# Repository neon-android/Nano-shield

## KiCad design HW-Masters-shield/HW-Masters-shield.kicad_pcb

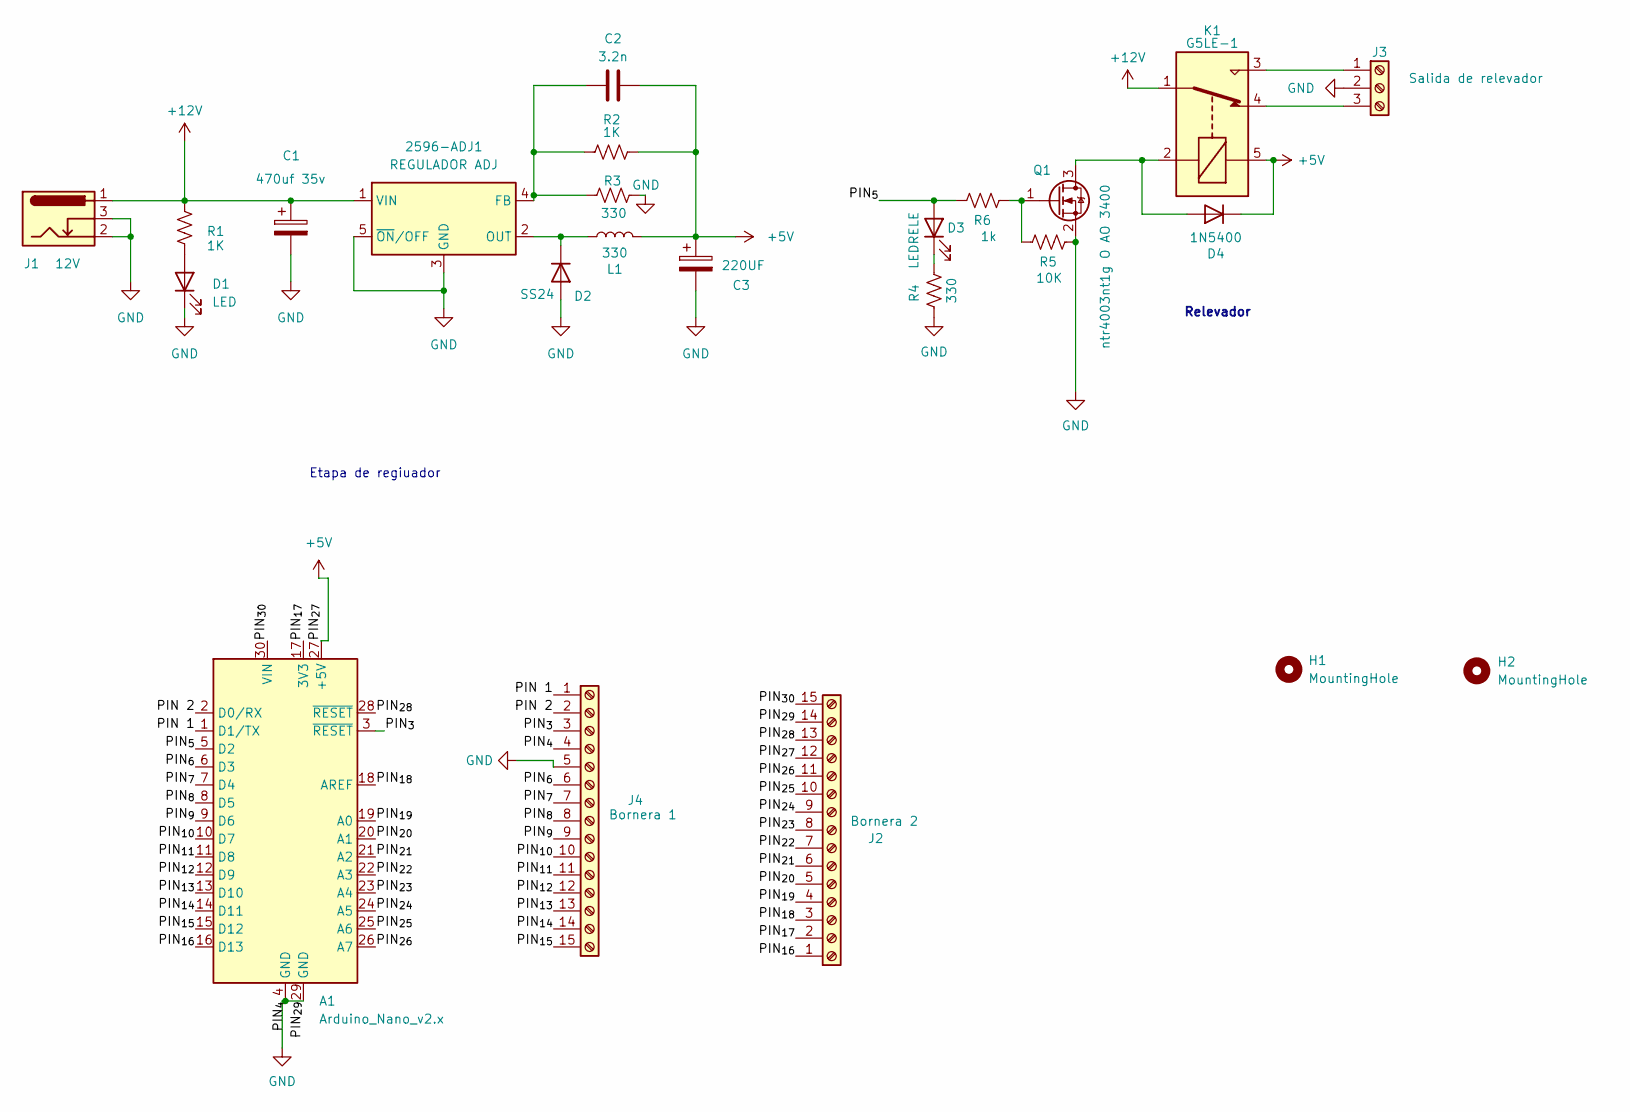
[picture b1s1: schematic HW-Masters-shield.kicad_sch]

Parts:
2596-ADJ1: REGULADOR ADJ; TO-263-5_TabPin3
A1: Arduino_Nano_v2.x; Arduino_Nano
C1: 470uf 35v; CP_Radial_D6.3mm_P2.50mm
C2: 3.2n; C_0805_2012Metric
C3: 220UF; CP_Radial_D6.3mm_P2.50mm
D1: LED; D_1206_3216Metric_Pad1.42x1.75mm_HandSolder
D2: SS24; D_SMA
D3: LEDRELE; D_1206_3216Metric_Pad1.42x1.75mm_HandSolder
D4: 1N5400; D_A-405_P7.62mm_Horizontal
H1, H2: MountingHole; MountingHole_3.2mm_M3_Pad_Via
J1: 12V; BarrelJack_Horizontal
J2: Bornera 2; Altech_AK100_1x15_P5.00mm
J3: Salida de relevador; Altech_AK100_1x03_P5.00mm
J4: Bornera 1; Altech_AK100_1x15_P5.00mm
K1: G5LE-1; Relay_SPDT_Omron-G5LE-1
L1: 330; L_Bourns-SRN1060
Q1: ntr4003nt1g O AO 3400; SOT-23
R1, R2: 1K; R_1206_3216Metric_Pad1.30x1.75mm_HandSolder
R3, R4: 330; R_1206_3216Metric_Pad1.30x1.75mm_HandSolder
R5: 10K; R_1206_3216Metric_Pad1.30x1.75mm_HandSolder
R6: 1k; R_1206_3216Metric_Pad1.30x1.75mm_HandSolder

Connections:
+5V: A1.27 (+5V), C2.2, C3.1, D4.1 (K), J2.12, K1.5, L1.2, R2.1
+12V: 2596-ADJ1.1 (VIN), C1.1, J1.1, K1.1, R1.1
/PIN 1: A1.1 (D1/TX), J4.1
/PIN 2: A1.2 (D0/RX), J4.2
/PIN_{3}: A1.3 (~RESET), J4.3
/PIN_{5}: A1.5 (D2), D3.2 (A), R6.1
/PIN_{6}: A1.6 (D3), J4.6
/PIN_{7}: A1.7 (D4), J4.7
/PIN_{8}: A1.8 (D5), J4.8
/PIN_{9}: A1.9 (D6), J4.9
/PIN_{10}: A1.10 (D7), J4.10
/PIN_{11}: A1.11 (D8), J4.11
/PIN_{12}: A1.12 (D9), J4.12
/PIN_{13}: A1.13 (D10), J4.13
/PIN_{14}: A1.14 (D11), J4.14
/PIN_{15}: A1.15 (D12), J4.15
/PIN_{16}: A1.16 (D13), J2.1
/PIN_{17}: A1.17 (3V3), J2.2
/PIN_{18}: A1.18 (AREF), J2.3
/PIN_{19}: A1.19 (A0), J2.4
/PIN_{20}: A1.20 (A1), J2.5
/PIN_{21}: A1.21 (A2), J2.6
/PIN_{22}: A1.22 (A3), J2.7
/PIN_{23}: A1.23 (A4), J2.8
/PIN_{24}: A1.24 (A5), J2.9
/PIN_{25}: A1.25 (A6), J2.10
/PIN_{26}: A1.26 (A7), J2.11
/PIN_{28}: A1.28 (~RESET), J2.13
/PIN_{30}: A1.30 (VIN), J2.15
GND: 2596-ADJ1.3 (GND), 2596-ADJ1.5 (~ON/OFF), A1.4 (GND), A1.29 (GND), C1.2, C3.2, D1.1 (K), D2.2 (A), J1.2, J1.3, J2.14, J3.2, J4.4, J4.5, Q1.2 (S), R3.2, R4.1, R5.2
unnamed: 2596-ADJ1.4 (FB), C2.1, R2.2, R3.1
unnamed: 2596-ADJ1.2 (OUT), D2.1 (K), L1.1
unnamed: D1.2 (A), R1.2
unnamed: D3.1 (K), R4.2
unnamed: D4.2 (A), K1.2, Q1.3 (D)
unnamed: J3.1, K1.3
unnamed: J3.3, K1.4
unnamed: Q1.1 (G), R5.1, R6.2

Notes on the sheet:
Etapa de regiuador
Relevador

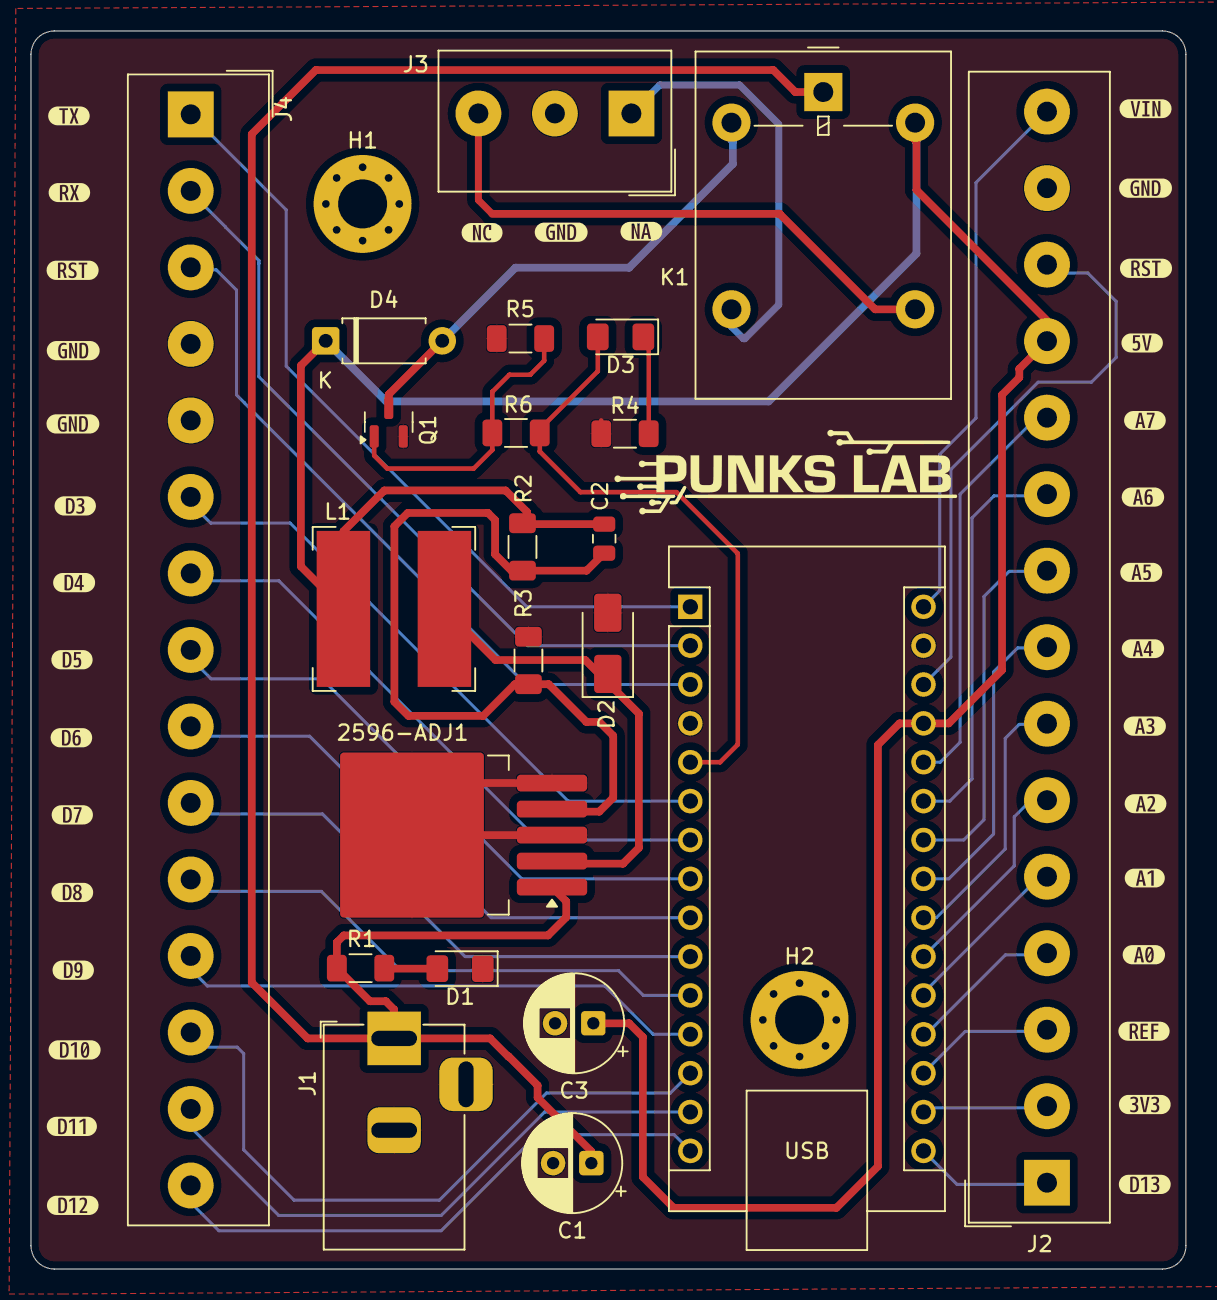
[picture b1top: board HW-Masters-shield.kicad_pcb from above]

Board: 2 copper layers, 75.5 x 80.9 mm, 57 parts (0 on the bottom side), 38 nets.

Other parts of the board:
kibuzzard-6A12559C: G***; kibuzzard-6A12559C
kibuzzard-69E52A8D: G***; kibuzzard-69E52A8D
kibuzzard-69E52A9B: G***; kibuzzard-69E52A9B
kibuzzard-69E52A31: G***; kibuzzard-69E52A31
kibuzzard-69E52A77: G***; kibuzzard-69E52A77
kibuzzard-69E52B09: G***; kibuzzard-69E52B09
kibuzzard-69E52B9F: G***; kibuzzard-69E52B9F
kibuzzard-69E52B16: G***; kibuzzard-69E52B16
kibuzzard-69E52B22: G***; kibuzzard-69E52B22
kibuzzard-69E52B35: G***; kibuzzard-69E52B35
kibuzzard-69E52B47: G***; kibuzzard-69E52B47
kibuzzard-69E52B52: G***; kibuzzard-69E52B52
kibuzzard-69E52B68: G***; kibuzzard-69E52B68
kibuzzard-69E52BB2: G***; kibuzzard-69E52BB2
kibuzzard-69E52BC8: G***; kibuzzard-69E52BC8
kibuzzard-69E52BEF: G***; kibuzzard-69E52BEF
kibuzzard-69E52BFA: G***; kibuzzard-69E52BFA
kibuzzard-69E52C0F: G***; kibuzzard-69E52C0F
kibuzzard-69E52C1C: G***; kibuzzard-69E52C1C
kibuzzard-69E52C05: G***; kibuzzard-69E52C05
kibuzzard-69E52C29: G***; kibuzzard-69E52C29
kibuzzard-69E52C38: G***; kibuzzard-69E52C38
kibuzzard-69E52C44: G***; kibuzzard-69E52C44
kibuzzard-69E52C52: G***; kibuzzard-69E52C52
kibuzzard-69E52C60: G***; kibuzzard-69E52C60
kibuzzard-69E52C80: G***; kibuzzard-69E52C80
kibuzzard-69E529B9: G***; kibuzzard-69E529B9
kibuzzard-69E529CF, kibuzzard-69E529CF#2: G***; kibuzzard-69E529CF
kibuzzard-69E5299A: G***; kibuzzard-69E5299A
kibuzzard-69E52917: G***; kibuzzard-69E52917
kibuzzard-69E52931: G***; kibuzzard-69E52931
kibuzzard-69E52989: G***; kibuzzard-69E52989

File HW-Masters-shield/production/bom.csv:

Designator,Footprint,Quantity,Value,LCSC Part #
2596-ADJ1,TO-263-5_TabPin3,1,REGULADOR ADJ,
A1,Arduino_Nano,1,Arduino_Nano_v2.x,
C1,CP_Radial_D6.3mm_P2.50mm,1,470uf 35v,
C2,0805,1,3.2n,
C3,CP_Radial_D6.3mm_P2.50mm,1,220UF,
D1,1206,1,LED,
D2,D_SMA,1,SS24,
D3,1206,1,LEDRELE,
D4,D_A-405_P7.62mm_Horizontal,1,1N5400,
J1,BarrelJack_Horizontal,1,12V,
J2,Altech_AK100_1x15_P5.00mm,1,Bornera 2,
J3,Altech_AK100_1x03_P5.00mm,1,Salida de relevador,
J4,Altech_AK100_1x15_P5.00mm,1,Bornera 1,
K1,Relay_SPDT_Omron-G5LE-1,1,G5LE-1,
L1,L_Bourns-SRN1060,1,330,
Q1,SOT-23,1,ntr4003nt1g O AO 3400,
"R1, R2, R6",1206,3,1K,
"R3, R4",1206,2,330,
R5,1206,1,10K,

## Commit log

2026-04-20 Se cea reposiorio y se suben archivos
2026-05-24 FEAT: crrijo error de mosfet y de falta de berreno de montaje
